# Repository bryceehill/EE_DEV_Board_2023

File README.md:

# EE_DEV_Board_2023
Files and Documentation for the Montana Tech EE Development Board

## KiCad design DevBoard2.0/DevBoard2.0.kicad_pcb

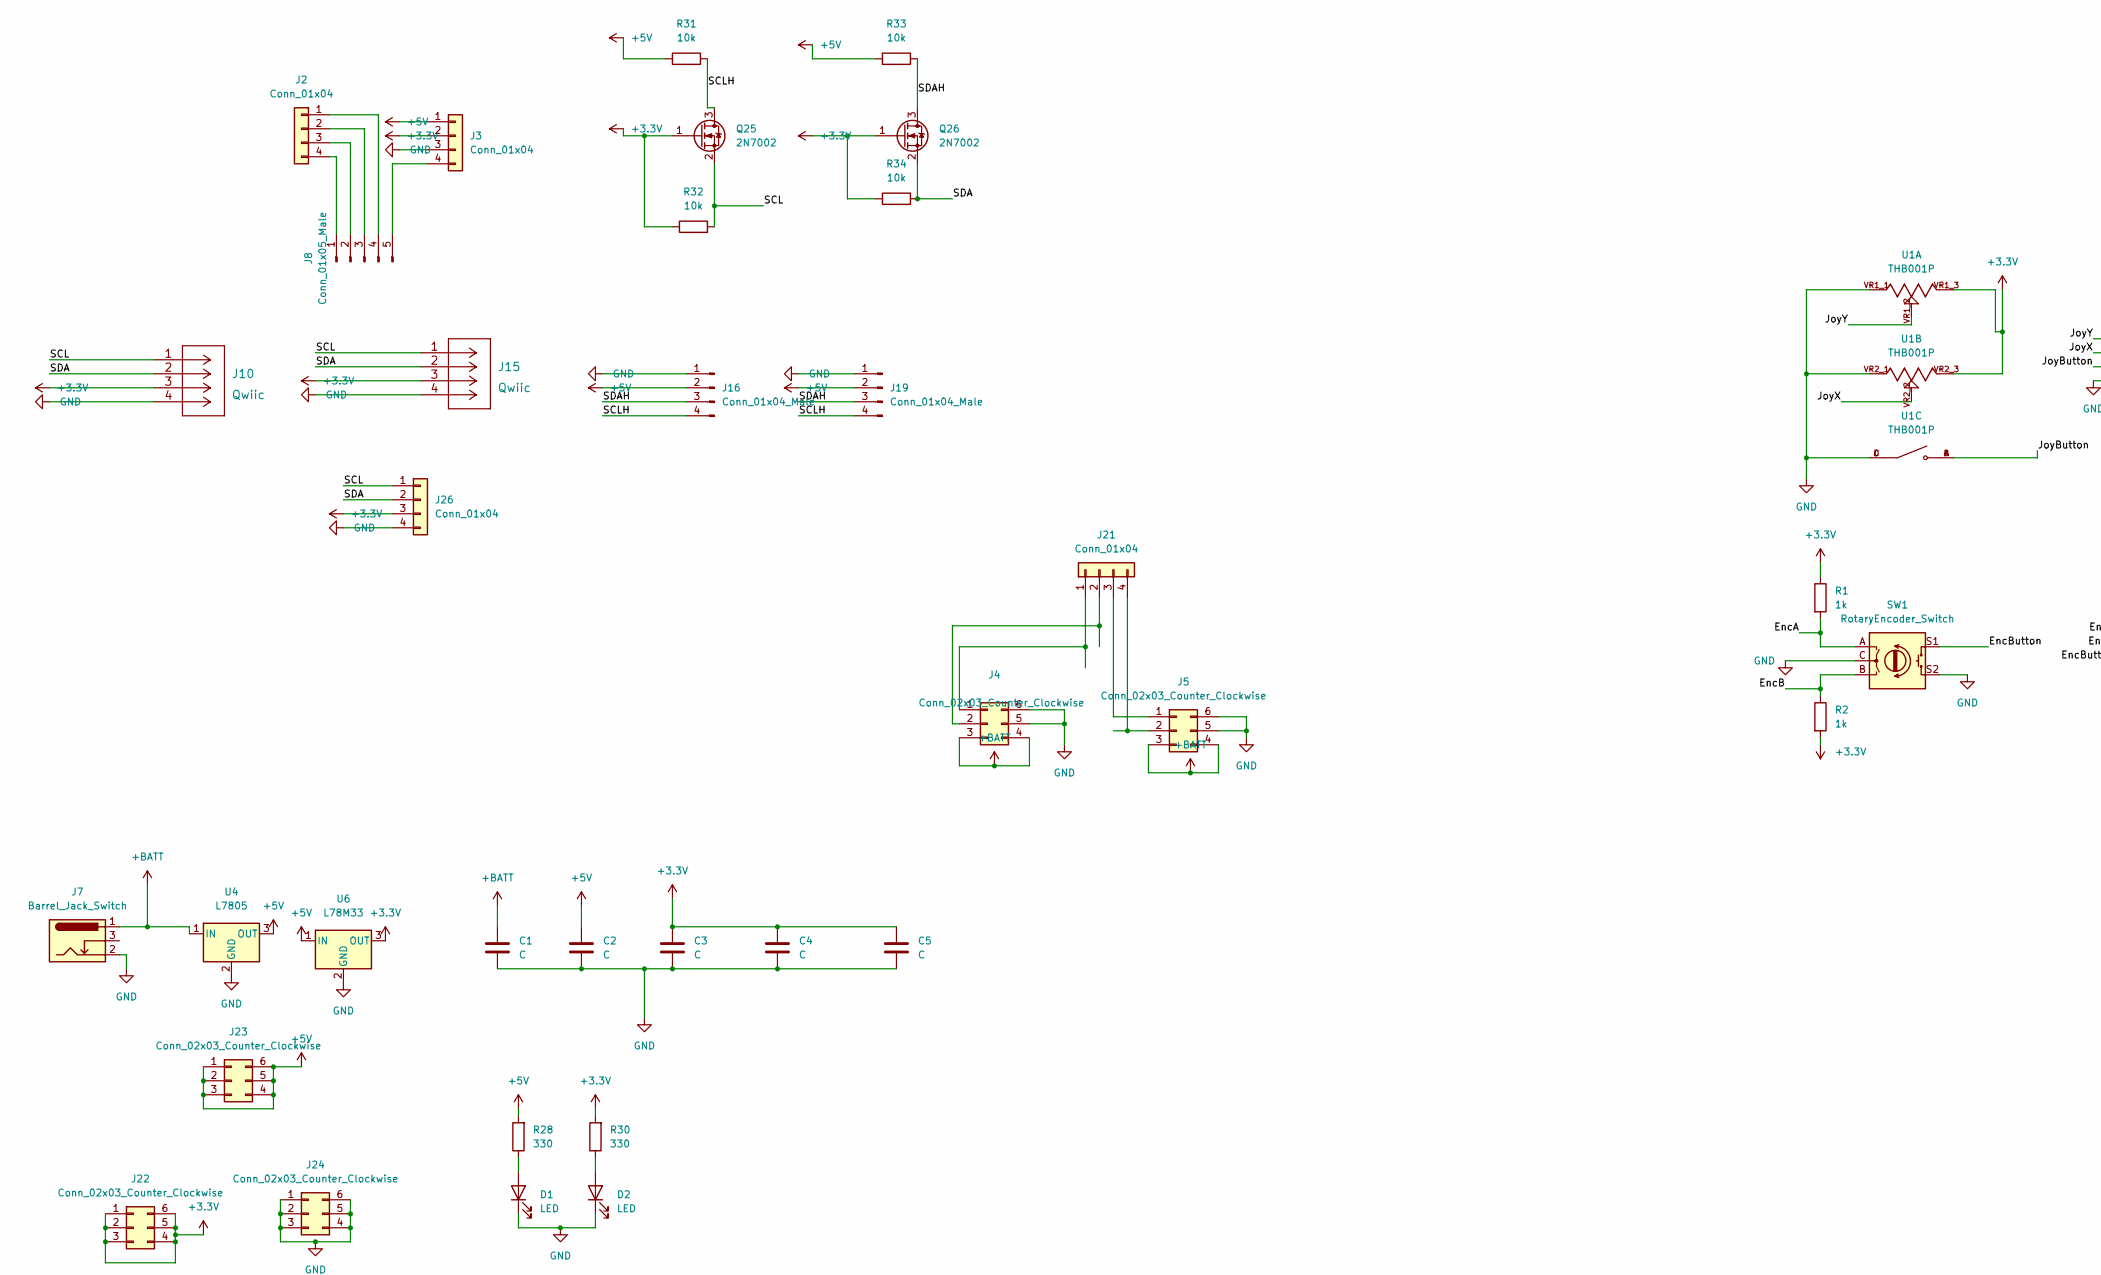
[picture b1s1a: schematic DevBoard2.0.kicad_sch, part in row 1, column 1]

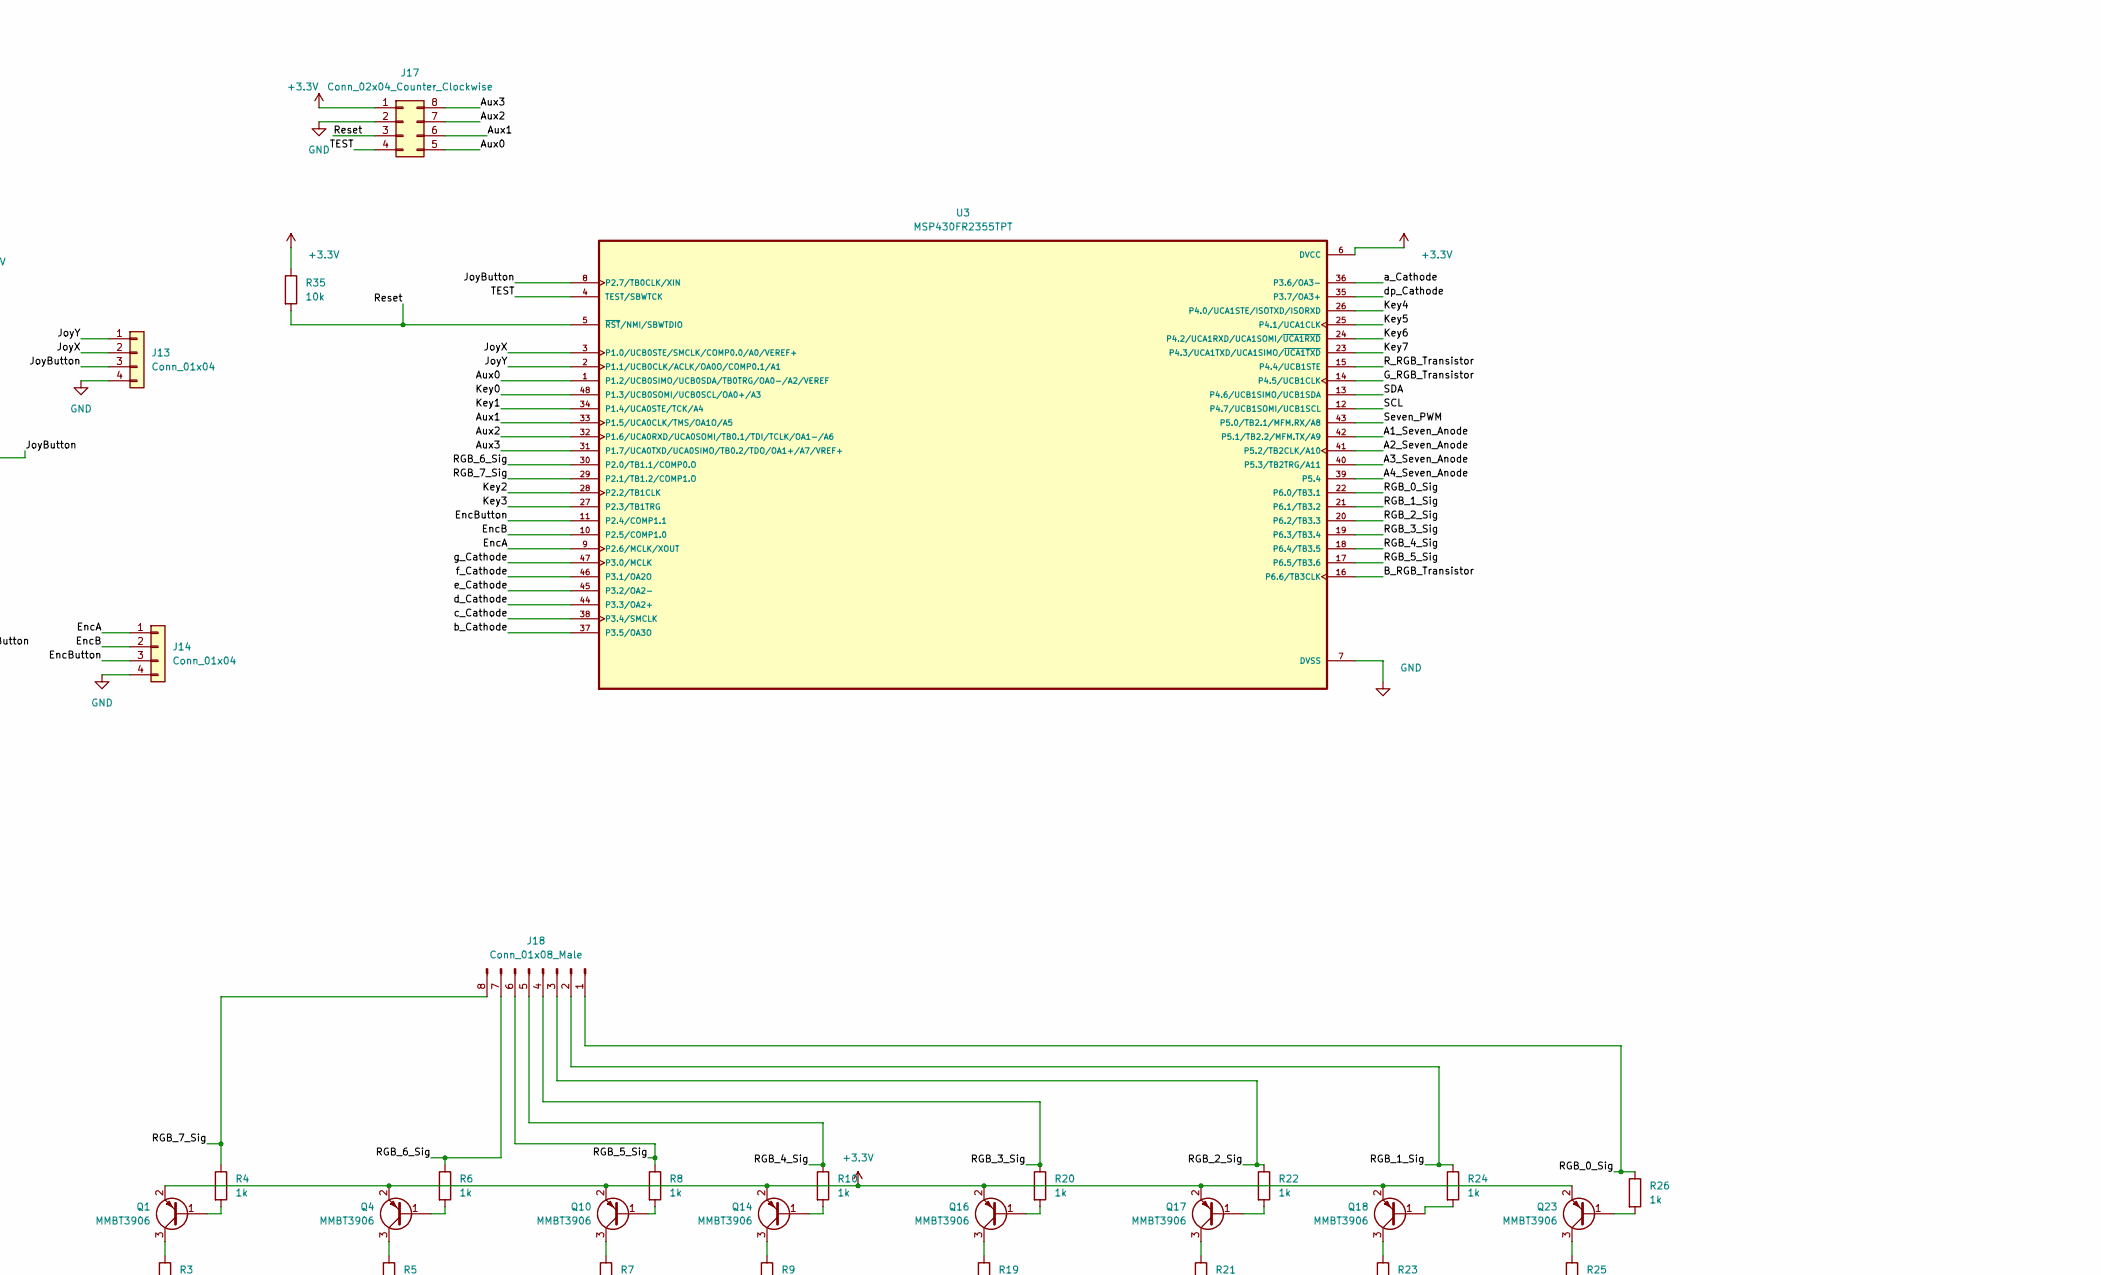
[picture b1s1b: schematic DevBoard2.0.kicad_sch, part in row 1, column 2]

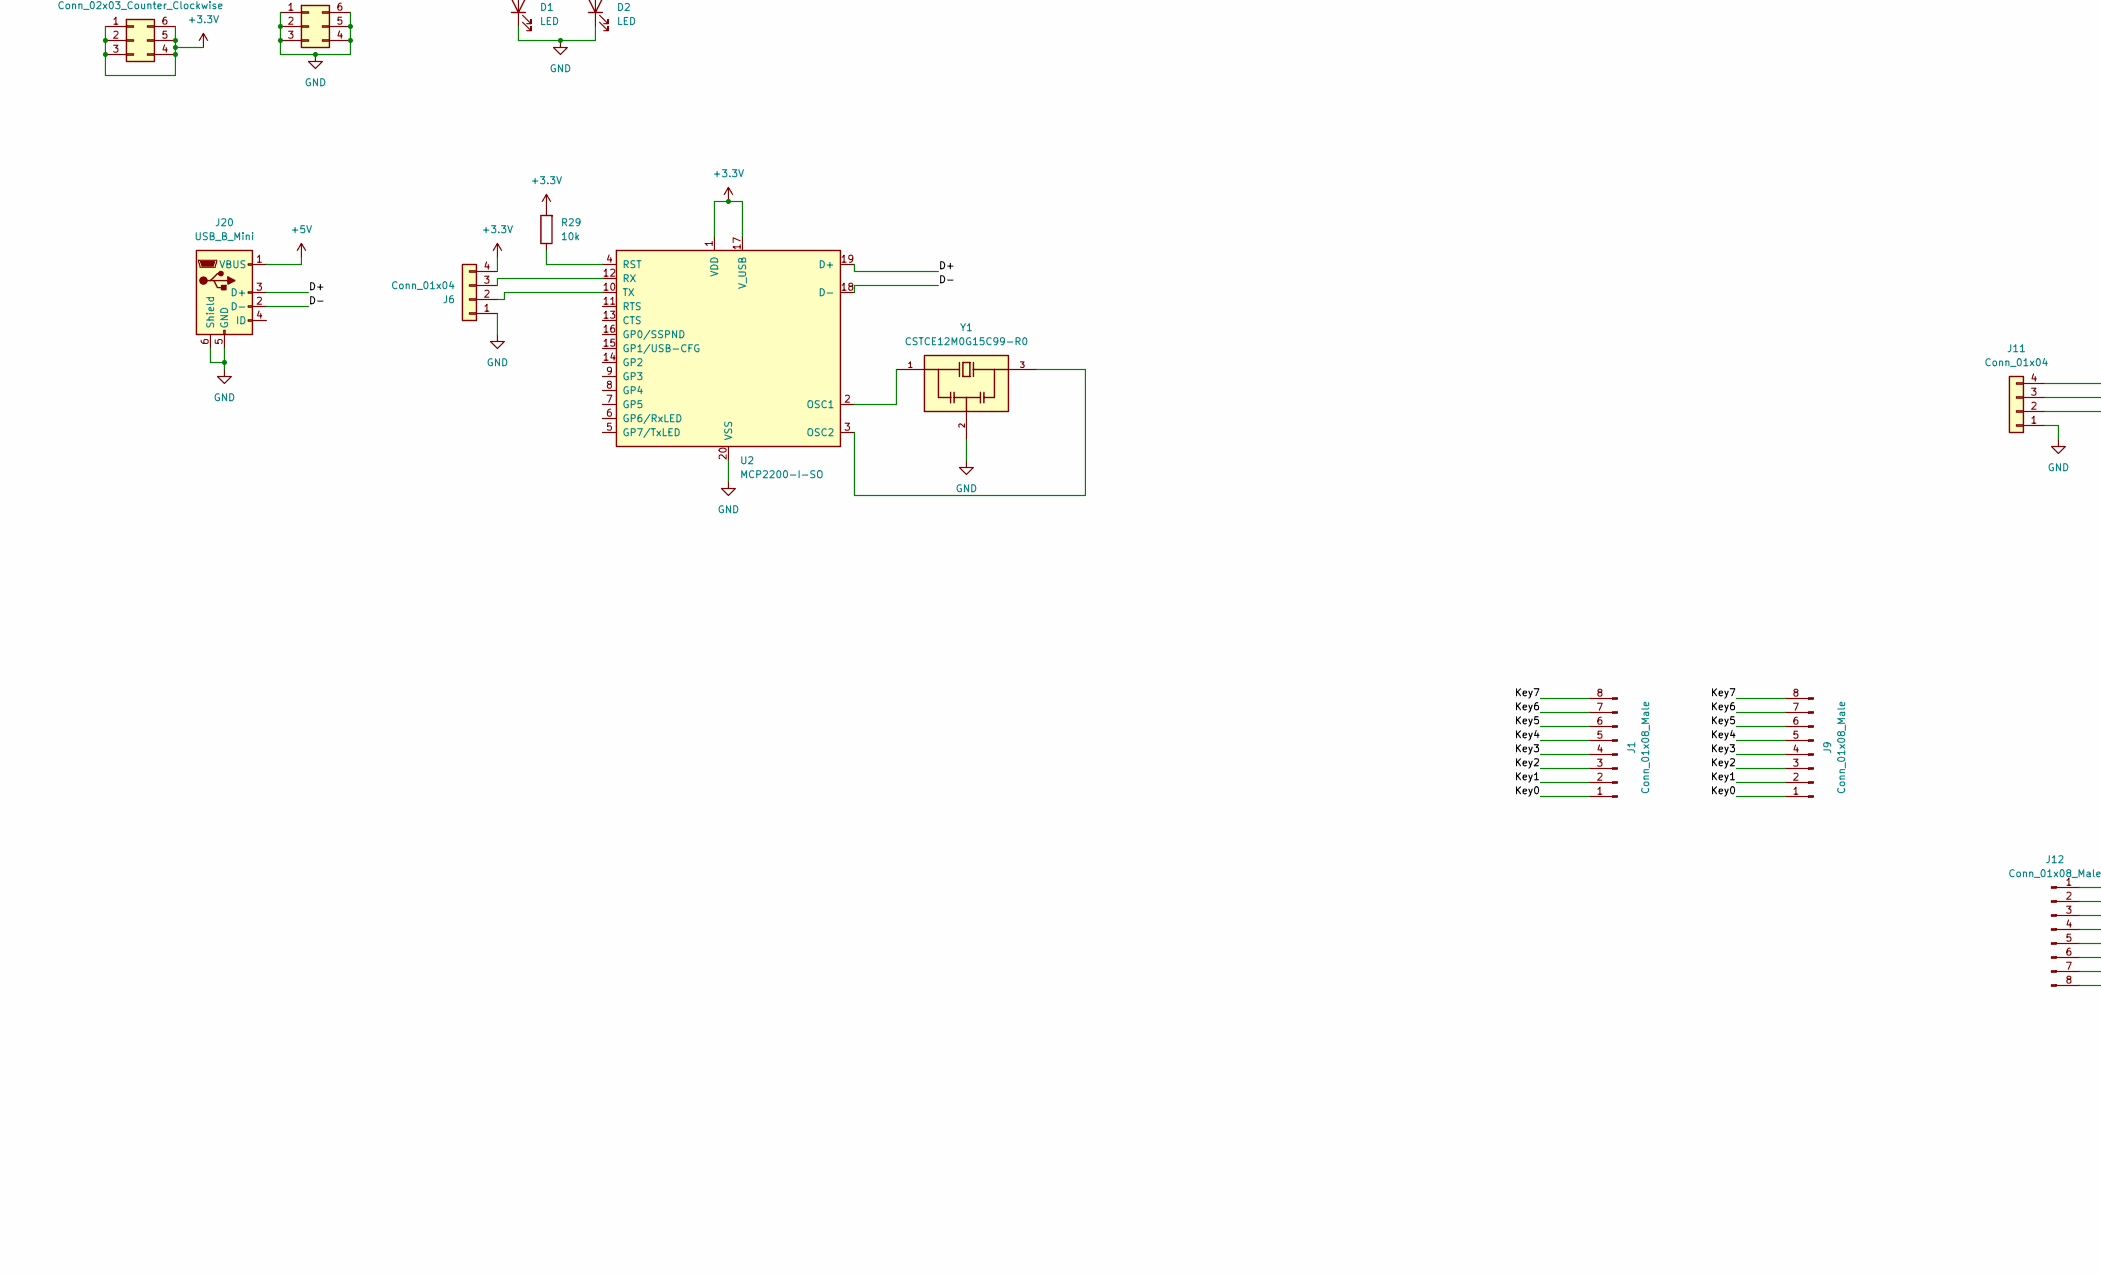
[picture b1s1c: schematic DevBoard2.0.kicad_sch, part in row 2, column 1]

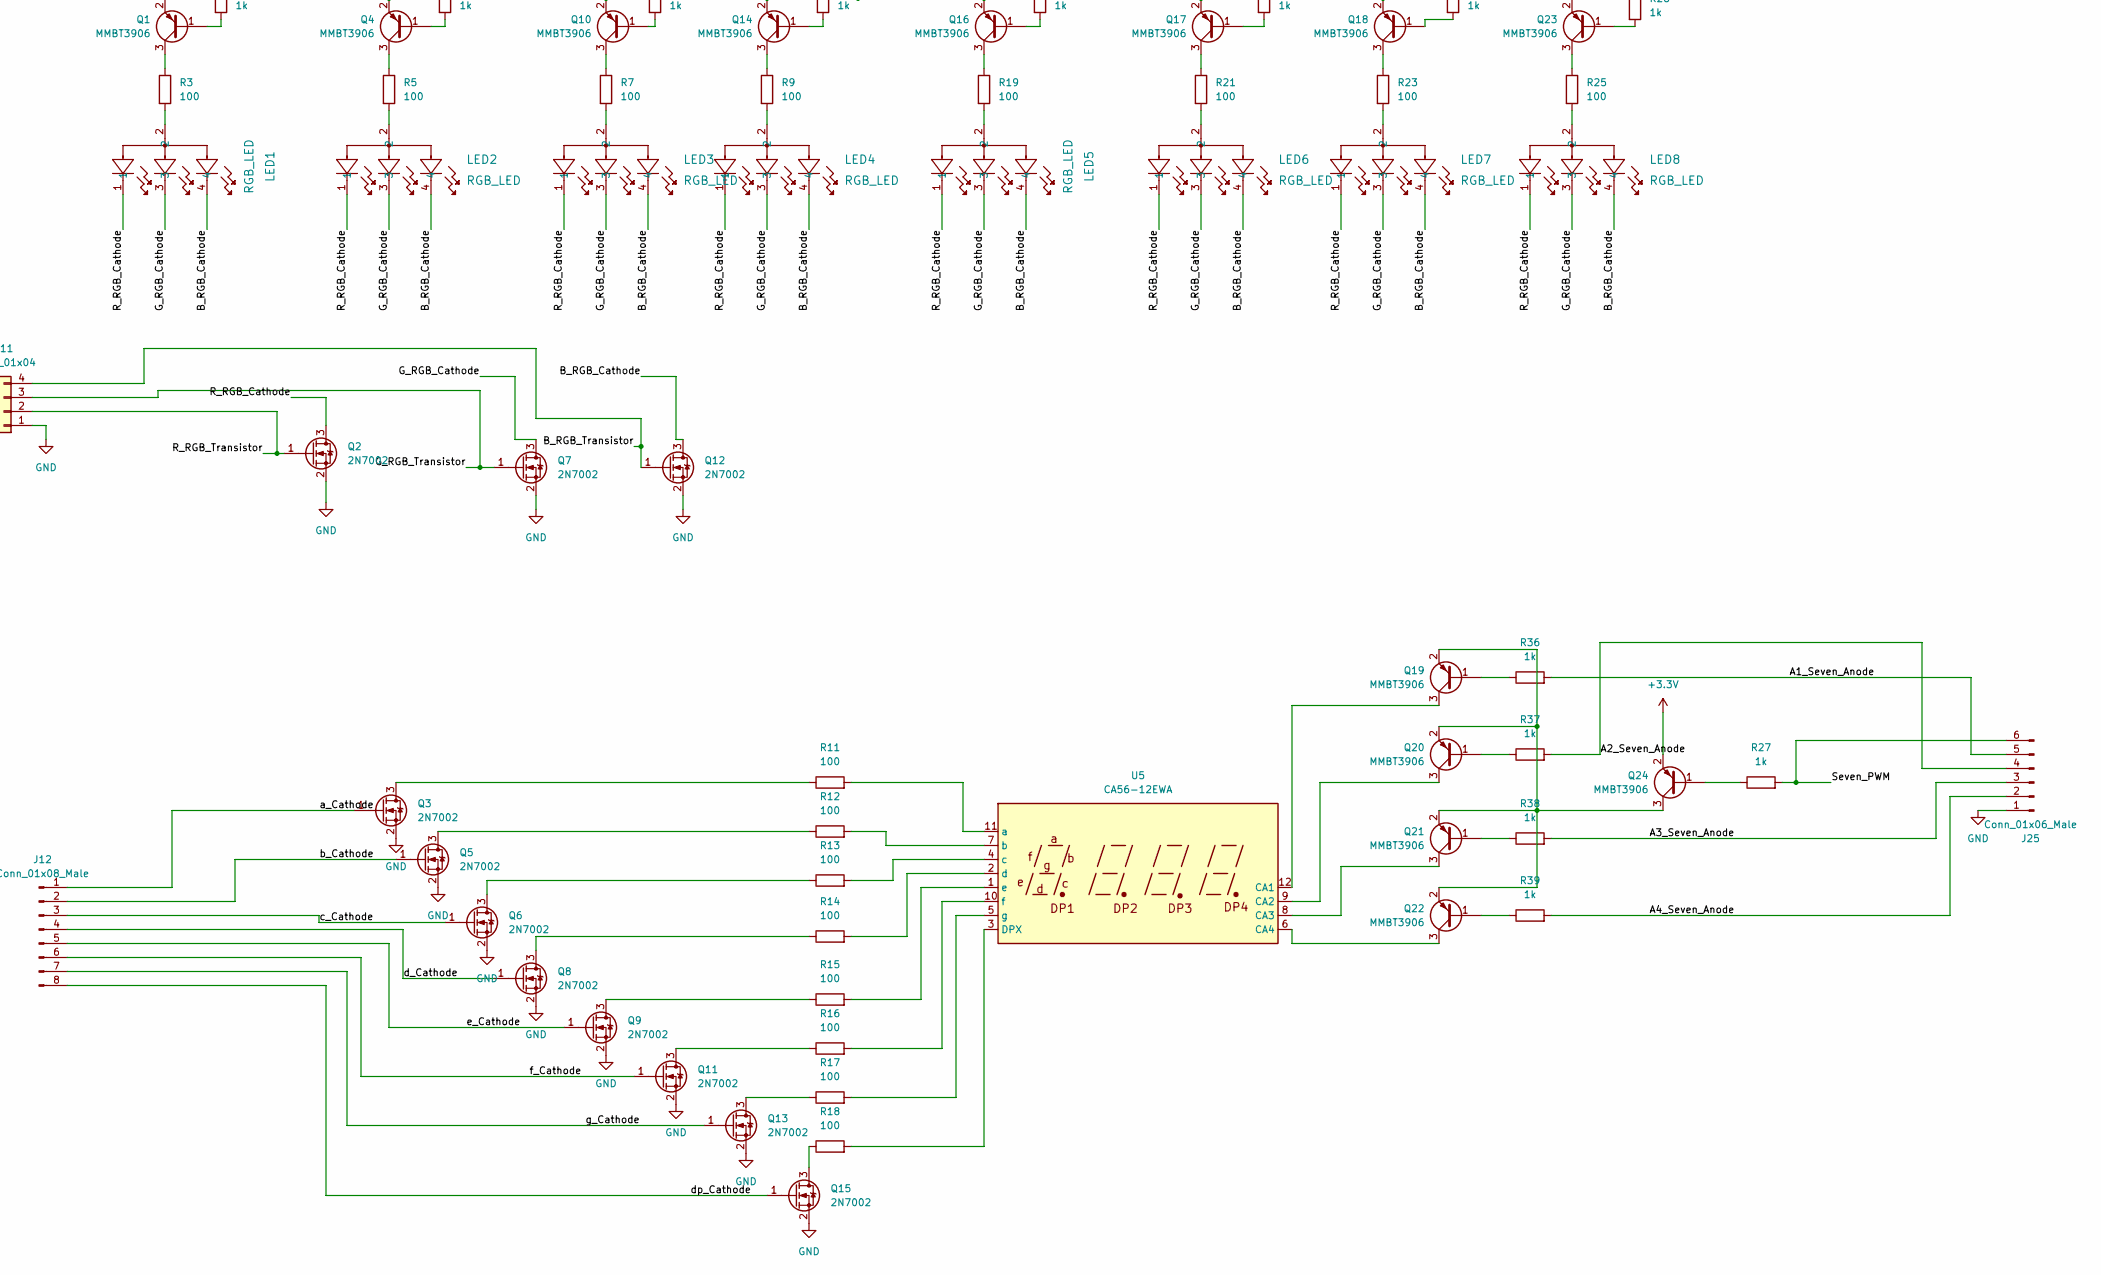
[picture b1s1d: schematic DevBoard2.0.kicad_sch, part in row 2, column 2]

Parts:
C1, C2, C3, C4, C5: C; C_0603_1608Metric
D1, D2: LED; LED_D5.0mm_FlatTop
J1, J12, J18: Conn_01x08_Male; PinHeader_1x08_P2.54mm_Vertical
J2, J3, J6, J11, J13, J14, J21, J26: Conn_01x04; PinHeader_1x04_P2.54mm_Vertical
J4, J5, J22, J23, J24: Conn_02x03_Counter_Clockwise; PinHeader_2x03_P2.54mm_Vertical
J7: Barrel_Jack_Switch; BarrelJack_Horizontal
J8: Conn_01x05_Male; PinHeader_1x05_P2.54mm_Vertical
J9: Conn_01x08_Male; PinHeader_1x08_P2.54mm_Horizontal
J10, J15: Qwiic; PRT-16766
J16, J19: Conn_01x04_Male; PinHeader_1x04_P2.54mm_Vertical
J17: Conn_02x04_Counter_Clockwise; PinHeader_2x04_P2.54mm_Vertical
J20: USB_B_Mini; USB_Mini-B_Tensility_54-00023_Vertical
J25: Conn_01x06_Male; PinHeader_1x06_P2.54mm_Vertical
LED1, LED2, LED3, LED4, LED5, LED6, LED7, LED8: RGB_LED; LED_WP154A4SEJ3VBDZGC&slash_CA_KNB
Q1, Q4, Q10, Q14, Q16, Q17, Q18, Q19, Q20, Q21, Q22, Q23, Q24: MMBT3906; SOT-23
Q2, Q3, Q5, Q6, Q7, Q8, Q9, Q11, Q12, Q13, Q15, Q25, Q26: 2N7002; SOT-23
R1, R2, R4, R6, R8, R10, R20, R22, R24, R26, R27, R36, R37, R38, R39: 1k; R_0603_1608Metric
R3, R5, R7, R9, R11, R12, R13, R14, R15, R16, R17, R18, R19, R21, R23, R25: 100; R_0603_1608Metric
R28, R30: 330; R_0603_1608Metric
R29, R31, R32, R33, R34, R35: 10k; R_0603_1608Metric
SW1: RotaryEncoder_Switch; PEC12R-4x15F-Sxxxx_BRN
U1: THB001P; CNK_THB001P; PARTREV 27 Jan 22
U2: MCP2200-I-SO; SOIC-20W_7.5x12.8mm_P1.27mm
U3: MSP430FR2355TPT; QFP50P900X900X160-48N
U4: L7805; TO-252-2
U5: CA56-12EWA
U6: L78M33; TO-252-2
Y1: CSTCE12M0G15C99-R0; OSC_CSTCE12M0G15C99-R0; PARTREV May 7, 2019

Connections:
+3V3: C3.1, C4.1, C5.1, J3.2, J6.4, J10.3, J15.3, J17.1, J22.1, J22.2, J22.3, J22.4, J22.5, J22.6, J26.3, Q1.2 (E), Q4.2 (E), Q10.2 (E), Q14.2 (E), Q16.2 (E), Q17.2 (E), Q18.2 (E), Q23.2 (E), Q24.2 (E), Q25.1 (G), Q26.1 (G), R1.1, R2.2, R29.2, R30.2, R32.1, R34.1, R35.1, U1.VR1_3, U1.VR2_3, U2.1 (VDD), U2.17 (V_USB), U3.6 (DVCC), U6.3 (OUT)
+5V: C2.1, J3.1, J16.2, J19.2, J20.1 (VBUS), J23.1, J23.2, J23.3, J23.4, J23.5, J23.6, R28.2, R31.1, R33.1, U4.3 (OUT), U6.1 (IN)
+BATT: C1.1, J4.3, J4.4, J5.3, J5.4, J7.1, U4.1 (IN)
/A1_Seven_Anode: J25.5, R36.2, U3.42 (P5.1/TB2.2/MFM.TX/A9)
/A2_Seven_Anode: J25.4, R37.2, U3.41 (P5.2/TB2CLK/A10)
/A3_Seven_Anode: J25.3, R38.2, U3.40 (P5.3/TB2TRG/A11)
/A4_Seven_Anode: J25.2, R39.2, U3.39 (P5.4)
/Aux0: J17.5, U3.1 (P1.2/UCB0SIMO/UCB0SDA/TB0TRG/OA0-/A2/VE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)
/Aux1: J17.6, U3.33 (P1.5/UCA0CLK/TMS/OA1O/A5)
/Aux2: J17.7, U3.32 (P1.6/UCA0RXD/UCA0SOMI/TB0.1/TDI/TCLK/OA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)
/Aux3: J17.8, U3.31 (P1.7/UCA0TXD/UCA0SIMO/TB0.2/TDO/OA1+/A7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)
/B_RGB_Cathode: LED1.4, LED2.4, LED3.4, LED4.4, LED5.4, LED6.4, LED7.4, LED8.4, Q12.3 (D)
/B_RGB_Transistor: J11.4, Q12.1 (G), U3.16 (P6.6/TB3CLK)
/D+: J20.3 (D+), U2.19 (D+)
/D-: J20.2 (D-), U2.18 (D-)
/EncA: J14.1, R1.2, SW1.A, U3.9 (P2.6/MCLK/XOUT)
/EncB: J14.2, R2.1, SW1.B, U3.10 (P2.5/COMP1.0)
/EncButton: J14.3, SW1.S1, U3.11 (P2.4/COMP1.1)
/G_RGB_Cathode: LED1.3, LED2.3, LED3.3, LED4.3, LED5.3, LED6.3, LED7.3, LED8.3, Q7.3 (D)
/G_RGB_Transistor: J11.3, Q7.1 (G), U3.14 (P4.5/UCB1CLK)
/JoyButton: J13.3, U1.A, U1.B, U3.8 (P2.7/TB0CLK/XIN)
/JoyX: J13.2, U1.VR2_2, U3.3 (P1.0/UCB0STE/SMCLK/COMP0.0/A0/VEREF+)
/JoyY: J13.1, U1.VR1_2, U3.2 (P1.1/UCB0CLK/ACLK/OA0O/COMP0.1/A1)
/Key0: J1.1, J9.1, U3.48 (P1.3/UCB0SOMI/UCB0SCL/OA0+/A3)
/Key1: J1.2, J9.2, U3.34 (P1.4/UCA0STE/TCK/A4)
/Key2: J1.3, J9.3, U3.28 (P2.2/TB1CLK)
/Key3: J1.4, J9.4, U3.27 (P2.3/TB1TRG)
/Key4: J1.5, J9.5, U3.26 (P4.0/UCA1STE/ISOTXD/ISORXD)
/Key5: J1.6, J9.6, U3.25 (P4.1/UCA1CLK)
/Key6: J1.7, J9.7, U3.24 (P4.2/UCA1RXD/UCA1SOMI/~UCA1RXD)
/Key7: J1.8, J9.8, U3.23 (P4.3/UCA1TXD/UCA1SIMO/~UCA1TXD)
/RGB_0_Sig: J18.1, R26.1, U3.22 (P6.0/TB3.1)
/RGB_1_Sig: J18.2, R24.1, U3.21 (P6.1/TB3.2)
/RGB_2_Sig: J18.3, R22.1, U3.20 (P6.2/TB3.3)
/RGB_3_Sig: J18.4, R20.1, U3.19 (P6.3/TB3.4)
/RGB_4_Sig: J18.5, R10.1, U3.18 (P6.4/TB3.5)
/RGB_5_Sig: J18.6, R8.1, U3.17 (P6.5/TB3.6)
/RGB_6_Sig: J18.7, R6.1, U3.30 (P2.0/TB1.1/COMP0.O)
/RGB_7_Sig: J18.8, R4.1, U3.29 (P2.1/TB1.2/COMP1.O)
/R_RGB_Cathode: LED1.1, LED2.1, LED3.1, LED4.1, LED5.1, LED6.1, LED7.1, LED8.1, Q2.3 (D)
/R_RGB_Transistor: J11.2, Q2.1 (G), U3.15 (P4.4/UCB1STE)
/Reset: J17.3, R35.2, U3.5 (~RST/NMI/SBWTDIO)
/SCL: J10.1, J15.1, J26.1, Q25.2 (S), R32.2, U3.12 (P4.7/UCB1SOMI/UCB1SCL)
/SCLH: J16.4, J19.4, Q25.3 (D), R31.2
/SDA: J10.2, J15.2, J26.2, Q26.2 (S), R34.2, U3.13 (P4.6/UCB1SIMO/UCB1SDA)
/SDAH: J16.3, J19.3, Q26.3 (D), R33.2
/Seven_PWM: J25.6, R27.2, U3.43 (P5.0/TB2.1/MFM.RX/A8)
/TEST: J17.4, U3.4 (TEST/SBWTCK)
/a_Cathode: J12.1, Q3.1 (G), U3.36 (P3.6/OA3-)
/b_Cathode: J12.2, Q5.1 (G), U3.37 (P3.5/OA3O)
/c_Cathode: J12.3, Q6.1 (G), U3.38 (P3.4/SMCLK)
/d_Cathode: J12.4, Q8.1 (G), U3.44 (P3.3/OA2+)
/dp_Cathode: J12.8, Q15.1 (G), U3.35 (P3.7/OA3+)
/e_Cathode: J12.5, Q9.1 (G), U3.45 (P3.2/OA2-)
/f_Cathode: J12.6, Q11.1 (G), U3.46 (P3.1/OA2O)
/g_Cathode: J12.7, Q13.1 (G), U3.47 (P3.0/MCLK)
GND: C1.2, C2.2, C3.2, C4.2, C5.2, D1.1 (K), D2.1 (K), J3.3, J4.5, J4.6, J5.5, J5.6, J6.1, J7.2, J10.4, J11.1, J13.4, J14.4, J15.4, J16.1, J17.2, J19.1, J20.5 (GND), J20.6 (Shield), J24.1, J24.2, J24.3, J24.4, J24.5, J24.6, J25.1, J26.4, Q2.2 (S), Q3.2 (S), Q5.2 (S), Q6.2 (S), Q7.2 (S), Q8.2 (S), Q9.2 (S), Q11.2 (S), Q12.2 (S), Q13.2 (S), Q15.2 (S), SW1.C, SW1.S2, U1.C, U1.D, U1.VR1_1, U1.VR2_1, U2.20 (VSS), U3.7 (DVSS), U4.2 (GND), U6.2 (GND), Y1.2
unnamed: D1.2 (A), R28.1
unnamed: D2.2 (A), R30.1
unnamed: J3.4, J8.5
unnamed: J4.2, J21.2
unnamed: J2.4, J8.1
unnamed: J2.3, J8.2
unnamed: J2.2, J8.3
unnamed: J2.1, J8.4
unnamed: J4.1, J21.1
unnamed: J5.1, J21.3
unnamed: J5.2, J21.4
unnamed: LED1.2, R3.2
unnamed: LED2.2, R5.2
unnamed: LED3.2, R7.2
unnamed: LED4.2, R9.2
unnamed: LED5.2, R19.2
unnamed: LED6.2, R21.2
unnamed: LED7.2, R23.2
unnamed: LED8.2, R25.2
unnamed: Q1.1 (B), R4.2
unnamed: Q1.3 (C), R3.1
unnamed: Q3.3 (D), R11.1
unnamed: Q4.1 (B), R6.2
unnamed: Q4.3 (C), R5.1
unnamed: Q5.3 (D), R12.1
unnamed: Q6.3 (D), R13.1
unnamed: Q8.3 (D), R14.1
unnamed: Q9.3 (D), R15.1
unnamed: Q10.1 (B), R8.2
unnamed: Q10.3 (C), R7.1
unnamed: Q11.3 (D), R16.1
unnamed: Q13.3 (D), R17.1
unnamed: Q14.1 (B), R10.2
unnamed: Q14.3 (C), R9.1
unnamed: Q15.3 (D), R18.1
unnamed: Q16.1 (B), R20.2
unnamed: Q16.3 (C), R19.1
unnamed: Q17.1 (B), R22.2
unnamed: Q17.3 (C), R21.1
unnamed: Q18.1 (B), R24.2
unnamed: Q18.3 (C), R23.1
unnamed: Q19.1 (B), R36.1
unnamed: Q19.2 (E), Q20.2 (E), Q21.2 (E), Q22.2 (E), Q24.3 (C)
unnamed: Q20.1 (B), R37.1
unnamed: Q21.1 (B), R38.1
unnamed: Q22.1 (B), R39.1
unnamed: Q23.1 (B), R26.2
unnamed: Q23.3 (C), R25.1
unnamed: Q24.1 (B), R27.1
unnamed: U2.2 (OSC1), Y1.1
unnamed: U2.3 (OSC2), Y1.3
unnamed: R29.1, U2.4 (RST)
unnamed: J6.2, U2.10 (TX)
unnamed: J6.3, U2.12 (RX)
unnamed: R15.2, U5.1 (e)
unnamed: R14.2, U5.2 (d)
unnamed: R18.2, U5.3 (DPX)
unnamed: R13.2, U5.4 (c)
unnamed: R17.2, U5.5 (g)
unnamed: Q22.3 (C), U5.6 (CA4)
unnamed: R12.2, U5.7 (b)
unnamed: Q21.3 (C), U5.8 (CA3)
unnamed: Q20.3 (C), U5.9 (CA2)
unnamed: R16.2, U5.10 (f)
unnamed: R11.2, U5.11 (a)
unnamed: Q19.3 (C), U5.12 (CA1)

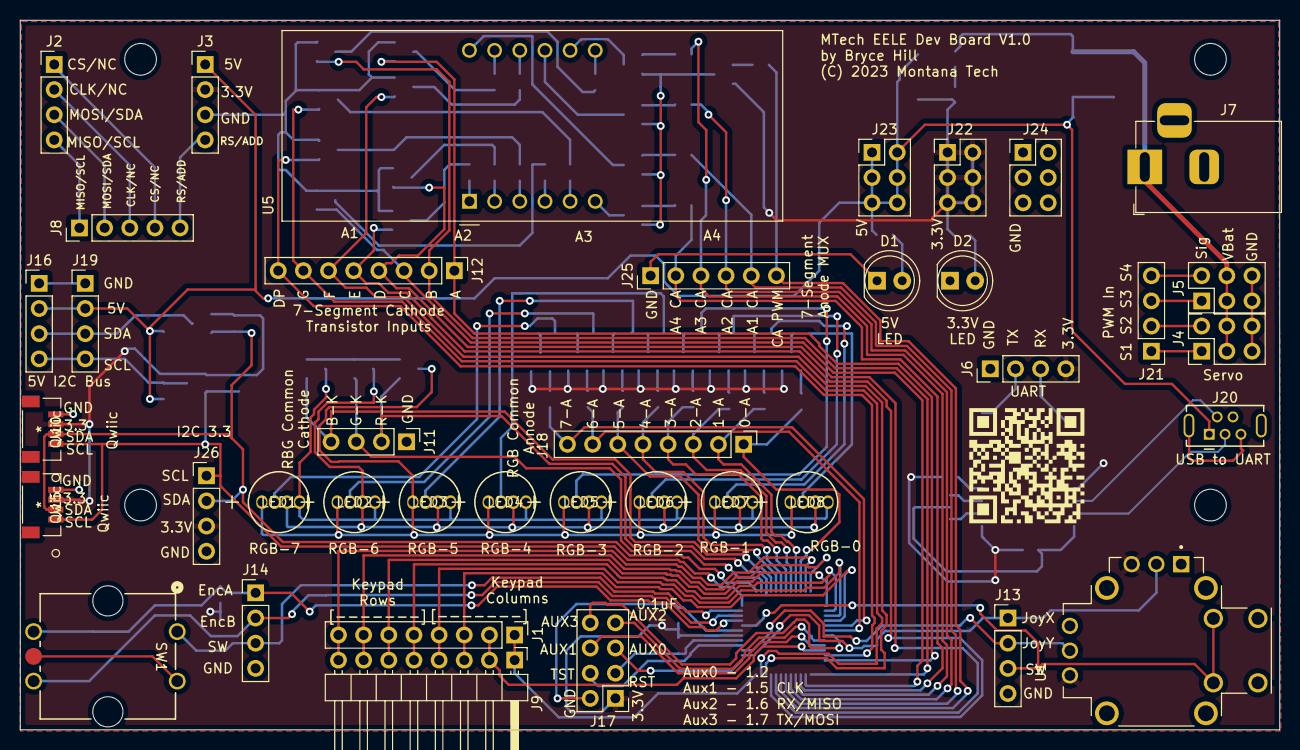
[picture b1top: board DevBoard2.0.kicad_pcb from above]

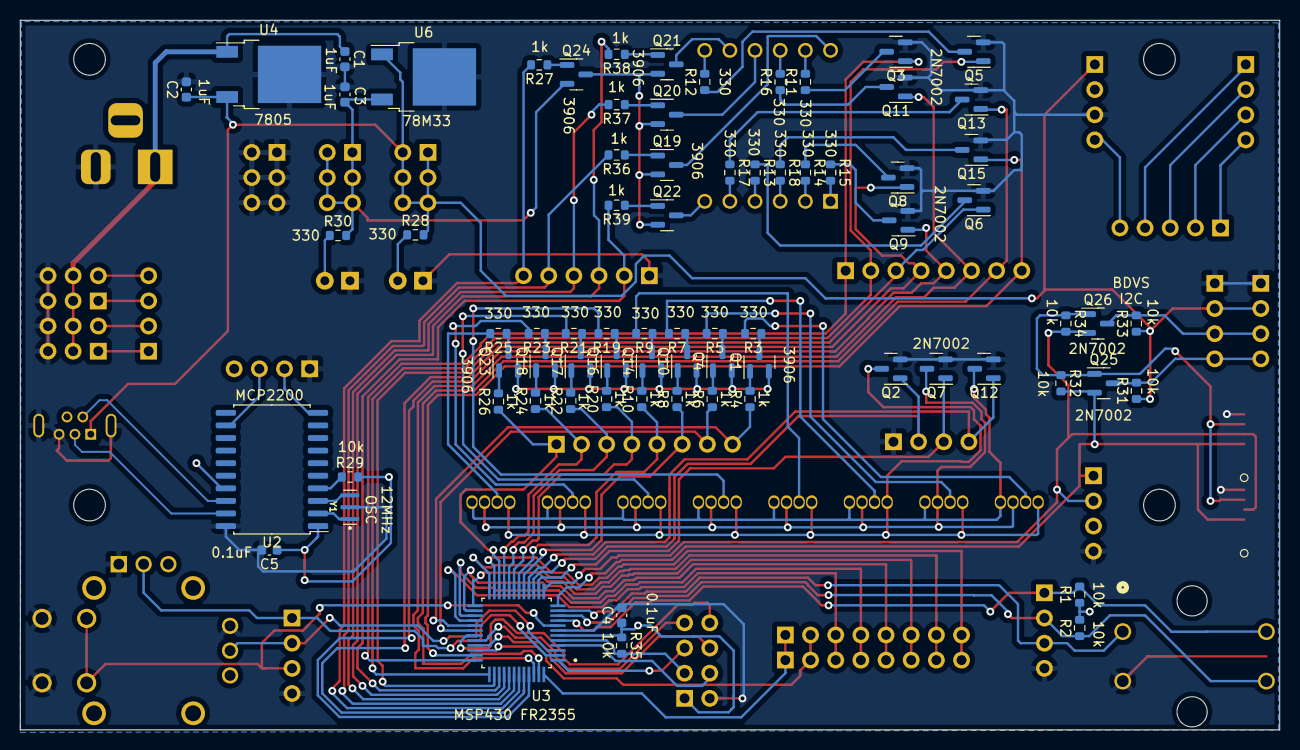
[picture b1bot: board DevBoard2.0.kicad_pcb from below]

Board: 2 copper layers, 127.1 x 71.6 mm, 114 parts (75 on the bottom side), 123 nets.

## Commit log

2023-08-30 Added Files for Dev2.0
    Initial images and KiCad files
2024-01-05 Dev Board Documentation PDF and Word Doc
    Lots of information about how to use the dev board.
2024-01-05 Full Schematic added

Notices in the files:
DevBoard2.0/DevBoard2.0.kicad_pcb:
(C) 2023 Montana Tech
parts and their libraries:
Copyright 2021 Accelerated Designs. All rights reserved.
